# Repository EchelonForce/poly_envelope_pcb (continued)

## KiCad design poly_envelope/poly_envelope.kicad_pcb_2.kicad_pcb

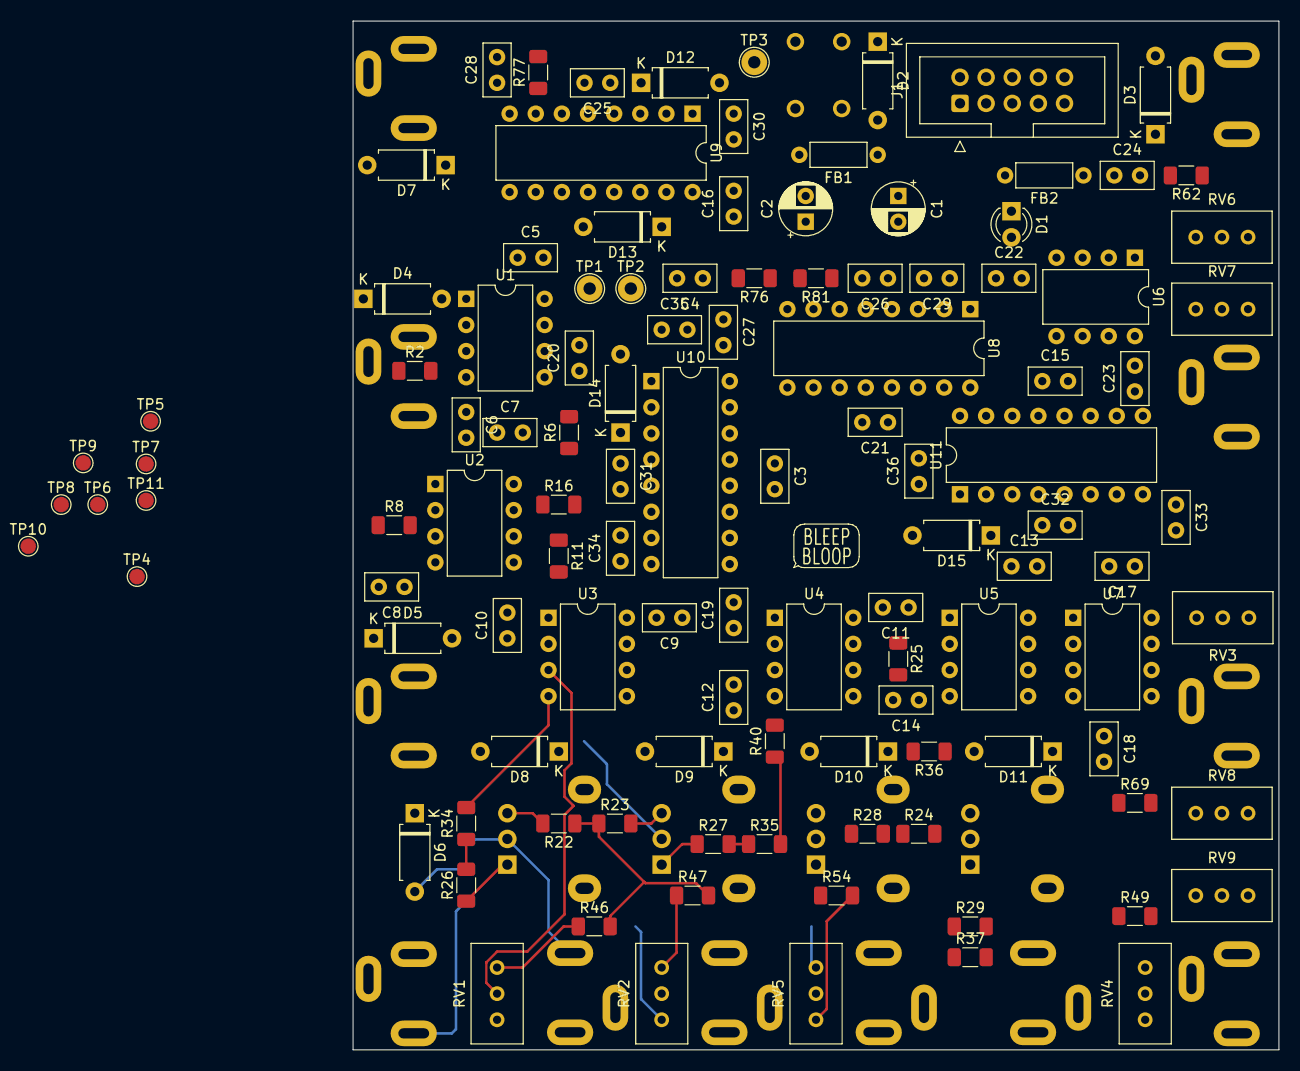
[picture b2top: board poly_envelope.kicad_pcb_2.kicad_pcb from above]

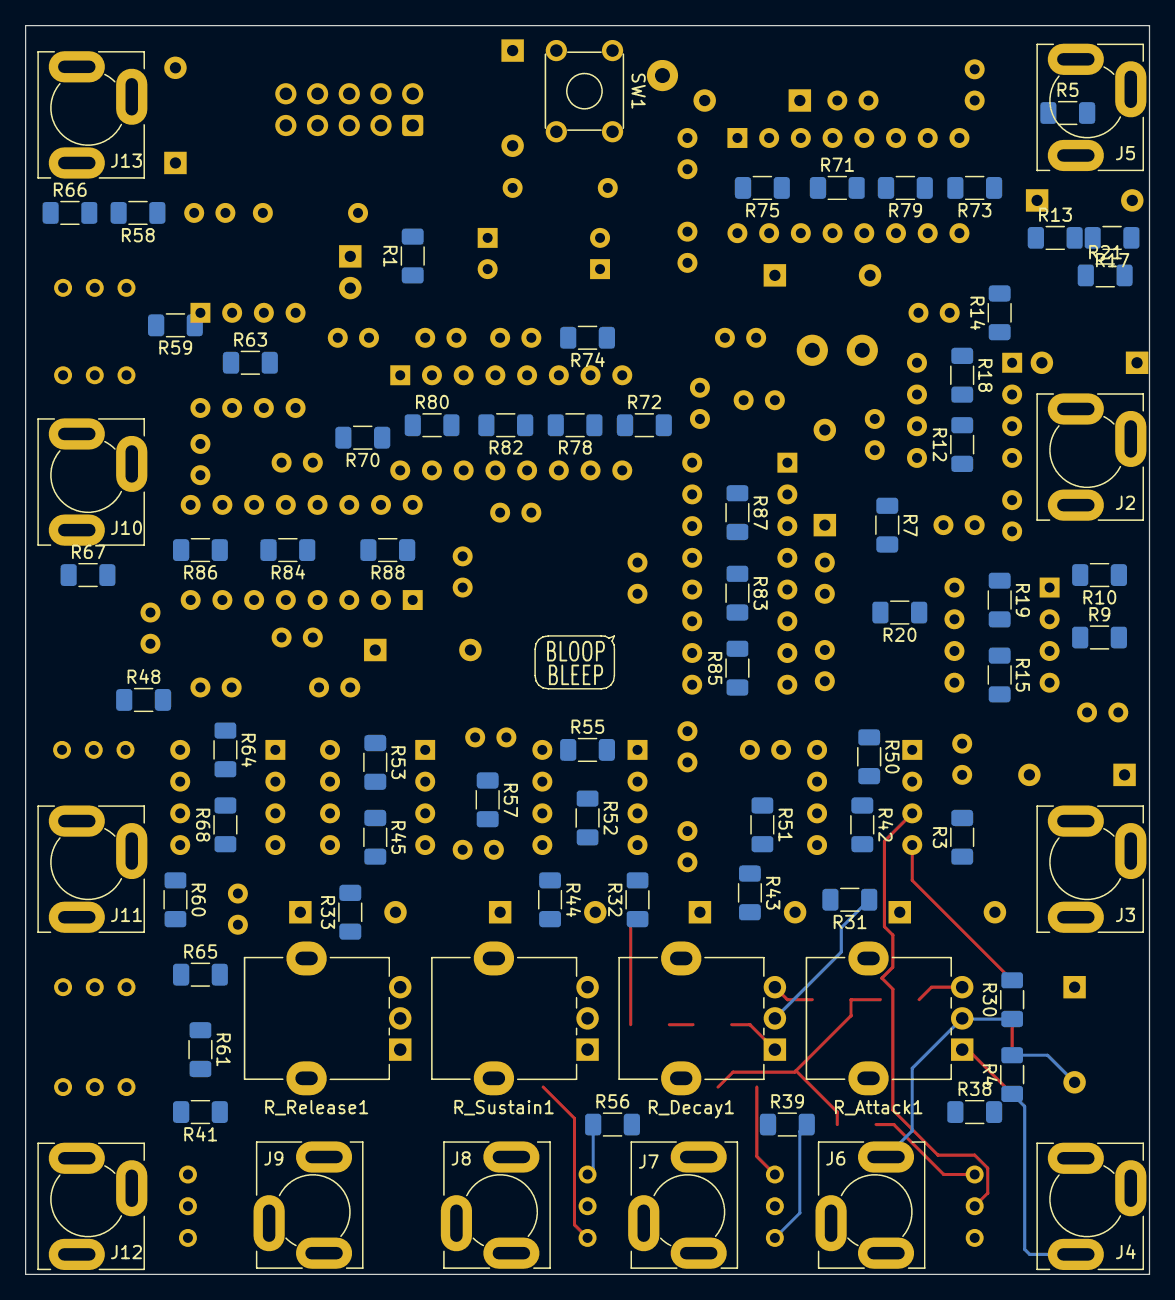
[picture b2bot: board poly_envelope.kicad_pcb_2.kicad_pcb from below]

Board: 2 copper layers, 90.0 x 100.0 mm, 193 parts (79 on the bottom side), 134 nets.

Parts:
C1, C2: 100uF; CP_Radial_D5.0mm_P2.50mm
C3, C4, C5, C6, C7, C8, C9, C10, C11, C12, C13, C14, C15, C16, C17, C18, C19, C20, C21, C22, C23, C24, C27, C28, C33, C34: 10nF; C_Disc_D5.0mm_W2.5mm_P2.50mm
C25, C26, C31, C32: 3nF; C_Disc_D5.0mm_W2.5mm_P2.50mm
C29, C30, C35, C36: 39nF; C_Disc_D5.0mm_W2.5mm_P2.50mm
D1: LED 1; LED_D3.0mm
D2, D3, D4, D5, D6, D7, D8, D9, D10, D11, D12, D13, D14, D15: D; D_A-405_P7.62mm_Horizontal
FB1, FB2: Ferrite_Bead_Small; L_Axial_L5.3mm_D2.2mm_P7.62mm_Horizontal_Vishay_IM-1
J1: Conn_02x05_Odd_Even; IDC-Header_2x05_P2.54mm_Vertical
J2: Gate_B; Jack_2.5mm_MJ-355W_Vertical
J3: Gate_C; Jack_2.5mm_MJ-355W_Vertical
J4: Gate_D; Jack_2.5mm_MJ-355W_Vertical
J5: Gate_A; Jack_2.5mm_MJ-355W_Vertical
J6: Attack_IN; Jack_2.5mm_MJ-355W_Vertical
J7: Decay_IN; Jack_2.5mm_MJ-355W_Vertical
J8: Sustain_IN; Jack_2.5mm_MJ-355W_Vertical
J9: Release_IN; Jack_2.5mm_MJ-355W_Vertical
J10: ENV_B; Jack_2.5mm_MJ-355W_Vertical
J11: ENV_C; Jack_2.5mm_MJ-355W_Vertical
J12: ENV_D; Jack_2.5mm_MJ-355W_Vertical
J13: ENV_A; Jack_2.5mm_MJ-355W_Vertical
LOGO1, LOGO2: logo1; Logo1
R1, R2, R3, R4, R5, R30, R31, R32, R33, R66, R67, R68, R69: 1k; R_1206_3216Metric_Pad1.30x1.75mm_HandSolder
R6, R8, R10, R12: 4.7k; R_1206_3216Metric_Pad1.30x1.75mm_HandSolder
R7, R9, R11, R13, R22, R23, R24, R25, R34, R35, R36, R37, R70, R71, R72, R73, R74, R75, R83, R84: 10k; R_1206_3216Metric_Pad1.30x1.75mm_HandSolder
R14, R15, R16, R17, R18, R19, R20, R21, R26, R27, R28, R29, R50, R51, R52, R53, R55, R57, R58, R59, R60, R61, R62, R63, R64, R65: 100k; R_1206_3216Metric_Pad1.30x1.75mm_HandSolder
R38, R39, R40, R41, R46, R47, R48, R49, R54, R56: 39k; R_1206_3216Metric_Pad1.30x1.75mm_HandSolder
R42, R43, R44, R45: 200k; R_1206_3216Metric_Pad1.30x1.75mm_HandSolder
R76, R77, R80, R81, R82, R85, R86: 470; R_1206_3216Metric_Pad1.30x1.75mm_HandSolder
R78, R79, R87, R88: 30k; R_1206_3216Metric_Pad1.30x1.75mm_HandSolder
RV1, RV2, RV3, RV4, RV5: 1k; Potentiometer_Bourns_3296W_Vertical
RV6, RV7, RV8, RV9: 100k; Potentiometer_Bourns_3296W_Vertical
R_Attack1: 100k; Potentiometer_Alpha_RD901F-40-00D_Single_Vertical
R_Decay1: 100k; Potentiometer_Alpha_RD901F-40-00D_Single_Vertical
R_Release1: 100k; Potentiometer_Alpha_RD901F-40-00D_Single_Vertical
R_Sustain1: 100k; Potentiometer_Alpha_RD901F-40-00D_Single_Vertical
SW1: SW_Push; SW_TH_Tactile_Omron_B3F-10xx
TP1: -12V; TestPoint_THTPad_D2.5mm_Drill1.2mm
TP2: GND; TestPoint_THTPad_D2.5mm_Drill1.2mm
TP3: +12V; TestPoint_THTPad_D2.5mm_Drill1.2mm
TP4: VP_A; TestPoint_Pad_D1.5mm
TP5: VP_C; TestPoint_Pad_D1.5mm
TP6: ATKOUT_A; TestPoint_Pad_D1.5mm
TP7: ATKOUT_C; TestPoint_Pad_D1.5mm
TP8: VP_B; TestPoint_Pad_D1.5mm
TP9: VP_D; TestPoint_Pad_D1.5mm
TP10: ATKOUT_B; TestPoint_Pad_D1.5mm
TP11: ATKOUT_D; TestPoint_Pad_D1.5mm
U1, U2, U3, U4, U5: LM358; DIP-8_W7.62mm
U6, U7: TL072; DIP-8_W7.62mm
U8, U9, U10, U11: AS3310; DIP-16_W7.62mm
X1: Level_Display_Front_Panel

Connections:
+12L: D3.2, J1.9, J1.10
+12V: C1.1, C3.2, C5.2, C7.2, C9.2, C11.2, C13.2, C15.2, C17.2, C19.2, C21.2, C23.2, FB2.2, R1.1, R22.1, R23.1, R24.1, R25.1, R46.2, R47.2, R48.2, R49.2, R54.1, RV6.1, RV7.1, RV8.1, RV9.1, SW1.1, TP3.1, U1.8, U2.8, U3.8, U4.8, U5.8, U6.8, U7.8, U8.11, U9.11, U10.11, U11.11
-12V: C2.2, C4.1, C6.1, C8.1, C10.1, C12.1, C14.1, C16.1, C18.1, C20.1, C22.1, C24.1, FB1.2, R34.2, R35.2, R36.2, R37.2, R38.1, R39.1, R40.1, R41.1, R56.2, R76.2, R77.2, R85.1, R86.2, RV6.3, RV7.3, RV8.3, RV9.3, TP1.1, U1.4, U2.4, U3.4, U4.4, U5.4, U6.4, U7.4
-12VA: D2.1, J1.1, J1.2
/EnvelopeGnerators/Attack: R50.1, R70.2, U3.1
/EnvelopeGnerators/Decay: R51.1, R71.1, U3.7
/EnvelopeGnerators/Gate_A: D13.2, R21.1, U1.1
/EnvelopeGnerators/Gate_B: D14.2, R18.1, U1.7
/EnvelopeGnerators/Gate_C: D12.2, R19.1, U2.1
/EnvelopeGnerators/Gate_D: D15.2, R20.1, U2.7
/EnvelopeGnerators/Release: R53.1, R75.2, U5.1
/EnvelopeGnerators/Sustain: R57.1, R72.2, U4.7
/Inputs/Gate_Switch: R6.1, R8.1, R10.1, R12.1, SW1.2
/Outputs/ENVELOPE_A: R78.1, U6.3, U8.2
/Outputs/ENVELOPE_B: R87.1, U6.5, U10.2
/Outputs/ENVELOPE_C: R79.1, U7.3, U9.2
/Outputs/ENVELOPE_D: R88.1, U7.5, U11.2
GND: C1.2, C2.1, C3.1, C4.2, C5.1, C6.2, C7.1, C8.2, C9.1, C10.2, C11.1, C12.2, C13.1, C14.2, C15.1, C16.2, C17.1, C18.2, C19.1, C20.2, C21.1, C22.2, C23.1, C24.2, C27.2, C28.2, C29.2, C30.2, C33.2, C34.2, C35.2, C36.2, D1.1, J1.3, J1.4, J1.5, J1.6, J1.7, J1.8, J2.R, J2.S, J3.R, J3.S, J4.R, J4.S, J5.R, J5.S, J6.R, J6.S, J7.R, J7.S, J8.R, J8.S, J9.R, J9.S, J10.R, J10.S, J11.R, J11.S, J12.R, J12.S, J13.R, J13.S, R7.2, R9.2, R11.2, R13.2, R14.2, R15.2, R16.2, R17.2, R73.2, R74.2, R80.2, R81.2, R82.2, R83.2, R84.2, TP2.1, U8.7, U8.14, U9.7, U9.14, U10.7, U10.14, U11.7, U11.14
unnamed: C25.1, D12.1, R73.1, U9.4
unnamed: C25.2, U9.5
unnamed: C26.1, D13.1, R74.1, U8.4
unnamed: C26.2, U8.5
unnamed: C27.1, U8.8
unnamed: C28.1, U9.8
unnamed: C29.1, U8.1
unnamed: C30.1, U9.1
unnamed: C31.1, D14.1, R83.1, U10.4
unnamed: C31.2, U10.5
unnamed: C32.1, D15.1, R84.1, U11.4
unnamed: C32.2, U11.5
unnamed: C33.1, U11.8
unnamed: C34.1, U10.8
unnamed: C35.1, U10.1
unnamed: C36.1, U11.1
unnamed: D1.2, R1.2
unnamed: D2.2, FB1.1
unnamed: D3.1, FB2.1
unnamed: D4.1, R6.2, R7.1, U1.5
unnamed: D4.2, R2.2
unnamed: D5.1, R8.2, R9.1, U2.3
unnamed: D5.2, R3.2
unnamed: D6.1, R10.2, R11.1, U2.5
unnamed: D6.2, R4.2
unnamed: D7.1, R12.2, R13.1, U1.3
unnamed: D7.2, R5.2
unnamed: D8.1, R42.2
unnamed: D8.2, R30.2
unnamed: D9.1, R43.2
unnamed: D9.2, R31.2
unnamed: D10.1, R44.2
unnamed: D10.2, R32.2
unnamed: D11.1, R45.2
unnamed: D11.2, R33.2
unnamed: J2.T, R2.1
unnamed: J3.T, R3.1
unnamed: J4.T, R4.1
unnamed: J5.T, R5.1
unnamed: J6.T, R30.1, R_Attack1.2
unnamed: J7.T, R31.1, R_Decay1.2
unnamed: J8.T, R32.1, R_Sustain1.2
unnamed: J9.T, R33.1, R_Release1.2
unnamed: J10.T, R67.1
unnamed: J11.T, R68.1
unnamed: J12.T, R69.1
unnamed: J13.T, R66.1
unnamed: R14.1, R18.2, U1.6
unnamed: R15.1, R19.2, U2.2
unnamed: R16.1, R20.2, U2.6
unnamed: R17.1, R21.2, U1.2
unnamed: R22.2, R_Attack1.3
unnamed: R23.2, R_Decay1.3
unnamed: R24.2, R_Sustain1.3
unnamed: R25.2, R_Release1.3
unnamed: R26.1, R_Attack1.1
unnamed: R26.2, R34.1
unnamed: R27.1, R_Decay1.1
unnamed: R27.2, R35.1
unnamed: R28.1, R_Sustain1.1
unnamed: R28.2, R36.1
unnamed: R29.1, R_Release1.1
unnamed: R29.2, R37.1
unnamed: R38.2, RV1.3
unnamed: R39.2, RV2.3
unnamed: R40.2, RV3.3
unnamed: R41.2, RV4.3
unnamed: R42.1, R50.2, U3.2
unnamed: R43.1, R51.2, U3.6
unnamed: R44.1, R52.2, U4.2
unnamed: R45.1, R53.2, U5.2
unnamed: R46.1, RV1.1
unnamed: R47.1, RV2.1
unnamed: R48.1, RV3.1
unnamed: R49.1, RV4.1
unnamed: R52.1, R55.2, U4.1
unnamed: R54.2, RV5.3
unnamed: R55.1, R57.2, U4.6
unnamed: R56.1, RV5.1
unnamed: R58.1, R62.2, U6.2
unnamed: R58.2, RV6.2
unnamed: R59.1, R63.2, U6.6
unnamed: R59.2, RV7.2
unnamed: R60.1, R64.2, U7.2
unnamed: R60.2, RV8.2
unnamed: R61.1, R65.2, U7.6
unnamed: R61.2, RV9.2
unnamed: R62.1, R66.2, U6.1
unnamed: R63.1, R67.2, U6.7
unnamed: R64.1, R68.2, U7.1
unnamed: R65.1, R69.2, U7.7
unnamed: R70.1, R80.1, U8.15, U9.15, U10.15, U11.15
unnamed: R71.2, R81.1, U8.12, U9.12, U10.12, U11.12
unnamed: R72.1, U8.9, U9.9, U10.9, U11.9
unnamed: R75.1, R82.1, U8.13, U9.13, U10.13, U11.13
unnamed: R76.1, U8.6
unnamed: R77.1, U9.6
unnamed: R78.2, U8.10
unnamed: R79.2, U9.10
unnamed: R85.2, U10.6
unnamed: R86.1, U11.6
unnamed: R87.2, U10.10
unnamed: R88.2, U11.10
unnamed: RV1.2, U3.3
unnamed: RV2.2, U3.5
unnamed: RV3.2, U4.3
unnamed: RV4.2, U5.3
unnamed: RV5.2, U4.5
unnamed: TP4.1, U8.3
unnamed: TP5.1, U9.3
unnamed: TP6.1, U8.16
unnamed: TP7.1, U9.16
unnamed: TP8.1, U10.3
unnamed: TP9.1, U11.3
unnamed: TP10.1, U10.16
unnamed: TP11.1, U11.16

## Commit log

2022-01-14 Initial commit with .gitignore
2022-07-10 Add README.md
2022-07-10 Simulation files and links
2022-07-10 V1 PCB as fabricated
    This is the version of the PCB ordered for v1.
2022-07-10 Front Panel CAD
